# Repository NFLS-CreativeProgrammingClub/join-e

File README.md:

# join-e
## 本项目开源，但是不允许商业，您可以随意更改，但是您更改后发布也请开源
一个简单的电池板

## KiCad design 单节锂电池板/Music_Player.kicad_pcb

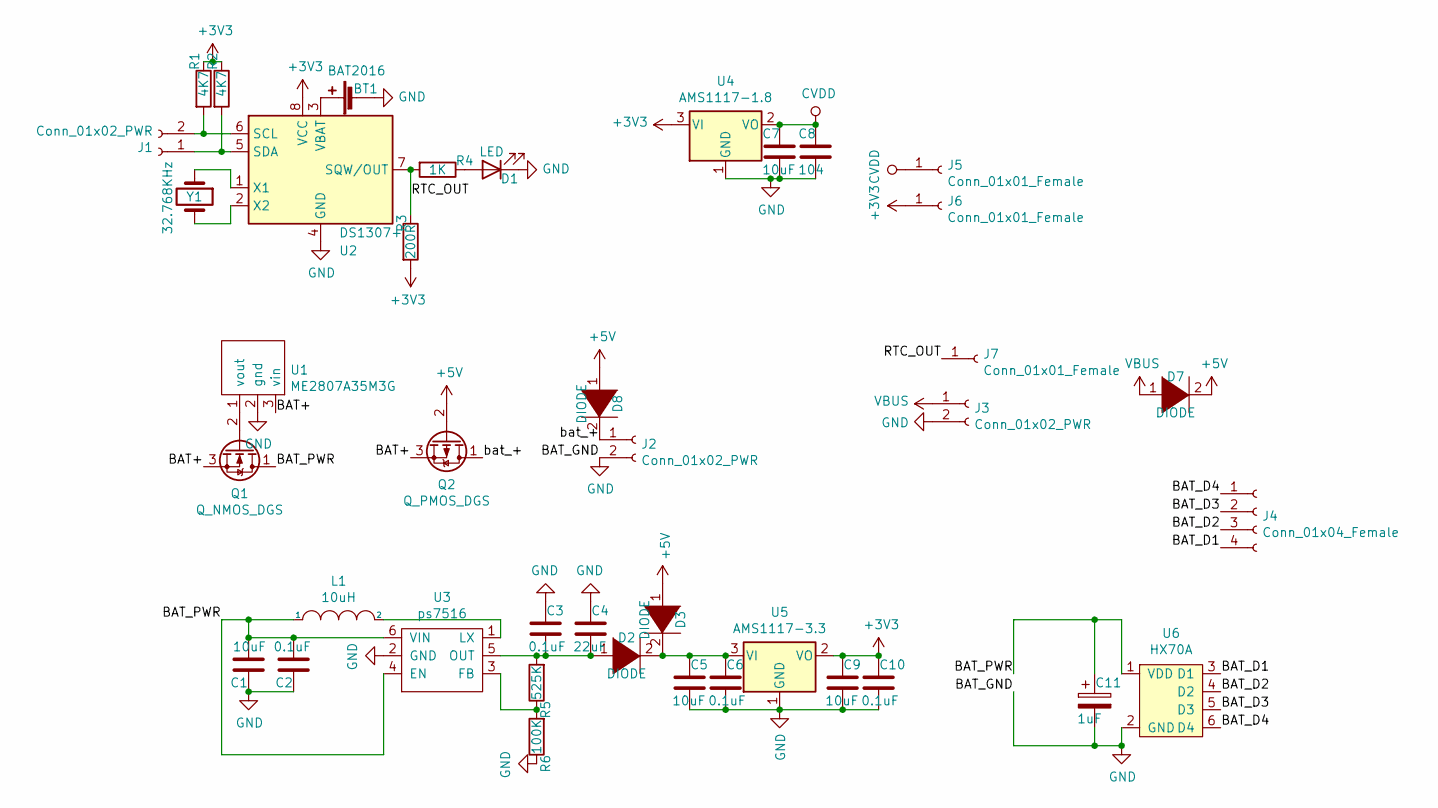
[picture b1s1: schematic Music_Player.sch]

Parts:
BT1: BAT2016; Battery_Panasonic_CR2032-VS1N_Vertical_CircularHoles
C1, C5, C7, C9: 10uF; C_0402_1005Metric
C2, C3, C6, C10: 0.1uF; C_0402_1005Metric
C4: 22uF; C_0402_1005Metric
C8: 104; C_0402_1005Metric
C11: 1uF; C_1206_3216Metric_Pad1.42x1.75mm_HandSolder
D1: LED; LED_0402_1005Metric
D2, D3, D7, D8: DIODE; D_0402_1005Metric
J1, J2, J3: Conn_01x02_PWR; PinSocket_1x02_P2.54mm_Vertical
J4: Conn_01x04_Female; PinSocket_1x04_P2.54mm_Vertical
J5, J6, J7: Conn_01x01_Female; PinSocket_1x01_P2.54mm_Vertical
L1: 10uH; 10uH电感 1a
Q1: Q_NMOS_DGS; SOT-23
Q2: Q_PMOS_DGS; SOT-23
R1, R2: 4K7; R_0402_1005Metric
R3: 200R; R_0402_1005Metric
R4: 1K; R_0402_1005Metric
R5: 525K; R_0402_1005Metric
R6: 100K; R_0402_1005Metric
U1: ME2807A35M3G; SOT-23
U2: DS1307+; DIP-8_W7.62mm
U3: ps7516; SOT-23-6_Handsoldering
U4: AMS1117-1.8; SOT-223
U5: AMS1117-3.3; SOT-223-3_TabPin2
U6: HX70A; SOT-23-6_Handsoldering
Y1: 32.768KHz; at-26

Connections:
+3V3: C9.1, C10.1, J6.1, R1.1, R2.1, R3.2, U2.8 (VCC), U4.3 (VI), U5.2 (VO)
+5V: D3.1 (K), D7.2 (A), D8.1 (K), Q2.2 (G)
/BAT+: Q1.3 (S), Q2.3 (S), U1.3 (vin)
/BAT_D1: J4.4, U6.3 (D1)
/BAT_D2: J4.3, U6.4 (D2)
/BAT_D3: J4.2, U6.5 (D3)
/BAT_D4: J4.1, U6.6 (D4)
/BAT_PWR: C1.2, C2.2, C11.1, L1.1, Q1.1 (D), U3.4 (EN), U3.6 (VIN), U6.1 (VDD)
/RTC_OUT: J7.1, R3.1, R4.2, U2.7 (SQW/OUT)
/bat_+: D8.2 (A), J2.1, Q2.1 (D)
CVDD: C7.1, C8.1, J5.1, U4.2 (VO), U4.4
GND: BT1.2 (-), C1.1, C2.1, C3.1, C4.1, C5.2, C6.2, C7.2, C8.2, C9.2, C10.2, C11.2, D1.1 (K), J2.2, J3.2, R6.1, U1.2 (gnd), U2.4 (GND), U3.2 (GND), U4.1 (GND), U5.1 (GND), U6.2 (GND)
unnamed: BT1.1 (+), U2.3 (VBAT)
unnamed: C3.2, C4.2, D2.1 (K), R5.2, U3.5 (OUT)
unnamed: C5.1, C6.1, D2.2 (A), D3.2 (A), U5.3 (VI)
unnamed: D1.2 (A), R4.1
unnamed: J1.1, R2.2, U2.5 (SDA)
unnamed: J1.2, R1.2, U2.6 (SCL)
unnamed: L1.2, U3.1 (LX)
unnamed: Q1.2 (G), U1.1 (vout)
unnamed: R5.1, R6.2, U3.3 (FB)
unnamed: U2.1 (X1), Y1.1
unnamed: U2.2 (X2), Y1.2
VBUS: D7.1 (K), J3.1

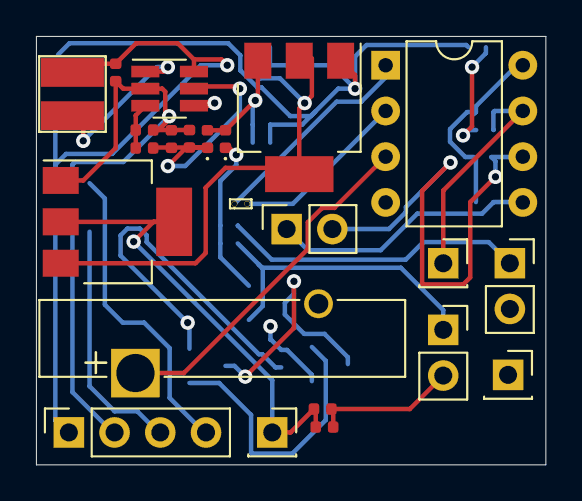
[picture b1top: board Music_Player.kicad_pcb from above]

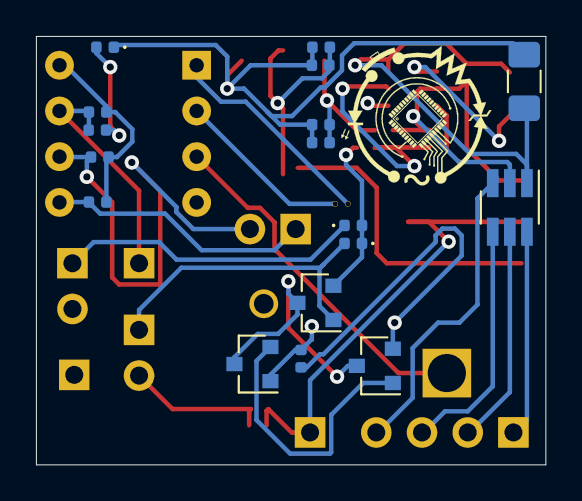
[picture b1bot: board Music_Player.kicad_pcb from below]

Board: 4 copper layers, 28.3 x 23.8 mm, 40 parts (17 on the bottom side), 24 nets.

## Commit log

2020-10-12 第一次更新
    还没有做外壳，但是电路部分搞完了，还没有美化
    这个电池板是单节锂电池适用3.7v那种
    稳定输出3.3v和1.8v
    可以用usb等5v充电
2020-10-15 第二次更新
    美化了一点点，缩小了一些
